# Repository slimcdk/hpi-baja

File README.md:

# Custom parts for HPI Baja 5B/T/SC

This repository contains sources to custom electronics/controller hardware with 3D-printable housings for HPI Baja 5B/T/SC as part of a electric conversion project.

## Contribution

Clone repository and fetch submodules

```bash
$ git clone --recursive-submodules git@github.com:slimcdk/wisweep.git
```

## Software uses

* https://www.kicad.org/
* https://www.freecadweb.org/
* https://github.com/features/actions
  <!-- * https://github.com/INTI-CMNB/KiBot -->
* https://code.visualstudio.com/
  * https://marketplace.visualstudio.com/items?itemName=ms-vscode-remote.remote-containers

* HPI Baja 5B 3D model by [Andi Hoxhaj](https://grabcad.com/andi.hoxhaj-1) https://grabcad.com/library/baja-5b-1

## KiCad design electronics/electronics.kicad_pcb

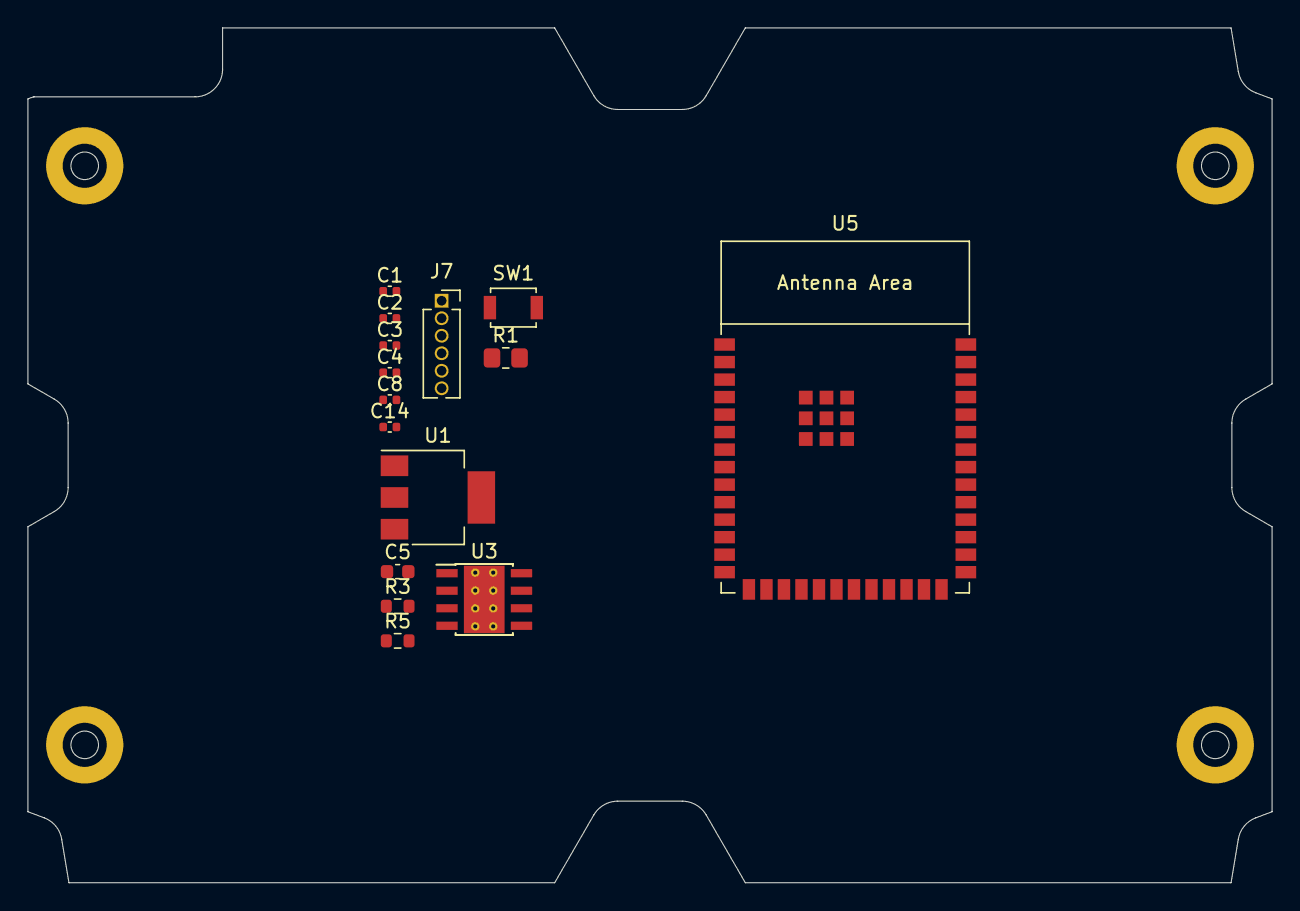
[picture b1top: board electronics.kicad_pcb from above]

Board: 2 copper layers, 90.2 x 62.0 mm, 19 parts (0 on the bottom side), 6 nets, no tracks yet.

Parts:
C1, C3: 1µF; C_0402_1005Metric
C2, C8, C14: 10µF; C_0402_1005Metric
C4: 100nF; C_0402_1005Metric
C5: 1µF; C_0603_1608Metric
H1, H2, H3, H4: M3 MountingHole; MountingHole_3.2mm_M3_DIN965_Pad
J7: Conn_01x06_Female; PinSocket_1x06_P1.27mm_Vertical
R1: 10K; R_0805_2012Metric_Pad1.20x1.40mm_HandSolder
R3, R5: 10k; R_0603_1608Metric
SW1: SW_Push; SW_SPST_B3U-1000P
U1: AMS1117-3.3; SOT-223-3_TabPin2
U3: LMR33640DDDA; Texas_HSOP-8-1EP_3.9x4.9mm_P1.27mm_ThermalVias
U5: ESP32-S3-WROOM-2

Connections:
+3V3: C2.2, C3.2, C4.2, C8.2, J7.4, R1.2, R3.1, R5.1, U1.2 (VO), U5.2 (3V3)
+5V: C14.2, U1.3 (VI)
/ESP_BOOT: J7.2, R5.2
/ESP_EN: C1.1, C5.1, J7.3, R1.1, R3.2, SW1.1, U5.3 (EN)
GND: C1.2, C2.1, C3.1, C4.1, C5.2, C8.1, C14.1, J7.1, SW1.2, U1.1 (GND), U3.1 (PGND), U3.9 (AGND), U5.1 (GND), U5.40 (GND), U5.41 (GND)
VDD: U3.2 (VIN), U3.3 (EN)

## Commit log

2020-06-13 initial work on hex hub, radio box and main frame profile
2020-06-13 added readme
2024-12-29 git ignore and modules update
2024-12-29 project cleanup
2024-12-29 added kicad library
